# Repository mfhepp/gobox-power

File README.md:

**Note:** This is work-in-progress. I will remove this message when the materials are ready for use.

# DC-DC Boost Converter with Input and Output Filter for QRP Transceivers
This project contains the necessary files and assembly instructions for a small PCB that includes a
a) DC-DC boost converter with effective input and output filters and a
b) battery voltage indicator circuit.

The board was designed for the [Mountain Topper SOTA GoBox](https://github.com/mfhepp/gobox) project, but can be used for any other similar project.

The boost converter is carefully designed to minimize RF emissions and noise on the output and output so that it does not impact the reception of weak radio signals in amateur radio transceivers. 

## Use with 4 NimH Cells ##
In the current form, the circuit will generate 6, 9 or 12 V from a 4 - 6 V input source, like four AA-sized NiMH batteries. This will give roughly 1 , 2.5 and 5 W output power with a Mountain Topper transceiver.

## Use with 2S Lipo Batteries ##
By modifying R4 and R5 one can also produce other voltages. The design can also be used with two LiPo cells, but then a simple SPST switch should be used for SW1 so that it optionally connects R5 parallel to R2. R4 can be omitted in this case, and only 9 or 12 V will be selectable.

You will also have to replace the Zener diode D3 to a type with Zener voltage of ca. 6.2 V so that the low battery warning will use the proper voltages for LiPos (see below).

## Input Current ##
The input current must not exceed 1.4 A, and the input voltage must be lower or equal to the lowest output voltage.

The input current is roughly the output current times the ratio of output voltage to input voltage plus the losses as the inverse of the efficiency (80 - 90%).

`input_current = output_current * output_voltage / (input_voltage * 0.85)`

**You also have to make sure that the battery used can handle the peak input current!!!** Check the datasheet of the battery before usage.

Design decisions will also be included in the final version.

## Low Battery Warning ##
The circuit includes a low battery warning component, but it is up to the user to actually turn of the circuit. As the battery voltages decreases, the red LED ("LOW1") wil start to light, and the green LED ("PWR1") will dim and eventually go out completely.

The exact voltage is determined by the Zener diode D3. For NiMH batteries with four cells, use a 3.9V type. For 2S LiPo packs, a 6.2V Zener diode might be a good choice.

**Warning 1:** You should turn off the device as soon as the green LED goes out completely, and switch back to the lower output voltages (6 or 9V) as soon as the red LED starts lighting. Otherwise, you will likely harm your battery, and because of the increasing input current needed to maintain the fixed output voltage, the circuit may overheat.

**Warning 2:** The battery voltage indicator does only consider the total series voltage of all battery cells. If there is an imbalance due to one or more cells being aged or damaged, the low battery warning will come too late. Thus, use the circuit only with factory-assembled multi-cell packs.

## Overview 
tbd

## Circuit Description 
tbd

## Ripple and Noice ##

Below, please find measurements of the remaining ripple and noise. The output voltage shows practically no ripple (less than 12mV Peak-to-Peak), the input voltage very little (ca. 66 mV Peak-to-Peak).

The parameters of the measurement were as follows:<br />
Input voltage: 9V from a 9V block battery.<br />
Load: 100 R resistor<br />
Output voltage: 11.9V<br />
Output current: 119 mA <br />

Measurements taken with a DMM and a Rigol Oscilloskope with a 1.10 probe.

**Input Voltage Ripple and Noise:** <br />

**Output Voltage Ripple and Noise:** <br />

## Part List
An Excel file that can be uploaded to Mouser's BOM tool is included in the repository at

https://github.com/mfhepp/gobox-power/raw/master/hardware/go-box-power.xlsx

## Assembly
**Note:** This is a densely packed PCB design using SMD components in size 0603, and for minimizing EMI, the pads do not have thermal relief, i.e. are directly connected to the copper of the ground signal and other signals. This makes soldering a bit challenging, and reworking even more so. In other words, this should not be your first exercise in SMD soldering....

The components are placed with minimal distances, so when hand-soldering, you need to think carefull about the ordering of components. Some pads will become hard to reach for hand-soldering once the adjacent component will have been added.

Because of the lack of thermal relief and the pads, you need to use a higher soldering temperature (I found 400 °C to work well), but this in turn means you have to work swiftly. I recommend a flat 1.2mm tip and a round 0.4 mm tip for the work. Preheating the PCB might be a good idea. You also need the finest rosin-core solder you can get hold of.

## Sources
The files in the repository contain 
* Gerber and drill files for producing your own PCBs, and
* a KiCad project with the schematics, PCB, and parts and footprints libraries.

KiCad is a great and free electronics design package. For more information, see [http://kicad.org/](http://kicad.org/).

## Acknowledgments
tbd

## Disclaimer 
THE SOFTWARE AND DESIGN ARE PROVIDED "AS IS", WITHOUT WARRANTY OF ANY KIND, EXPRESS OR IMPLIED, INCLUDING BUT NOT LIMITED TO THE WARRANTIES OF MERCHANTABILITY, FITNESS FOR A PARTICULAR PURPOSE AND NONINFRINGEMENT. IN NO EVENT SHALL THE AUTHORS OR COPYRIGHT HOLDERS BE LIABLE FOR ANY CLAIM, DAMAGES OR OTHER LIABILITY, WHETHER IN AN ACTION OF CONTRACT, TORT OR OTHERWISE, ARISING FROM, OUT OF OR IN CONNECTION WITH THE SOFTWARE OR DESIGN OR THE USE OR OTHER DEALINGS IN THE SOFTWARE OR DESIGN.

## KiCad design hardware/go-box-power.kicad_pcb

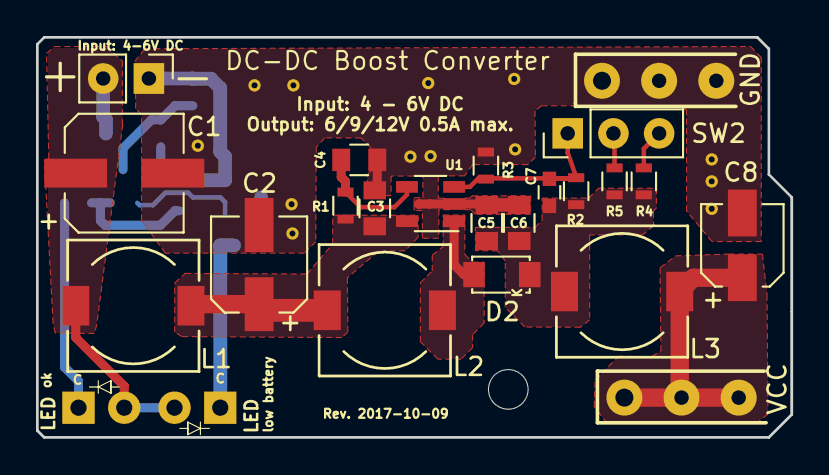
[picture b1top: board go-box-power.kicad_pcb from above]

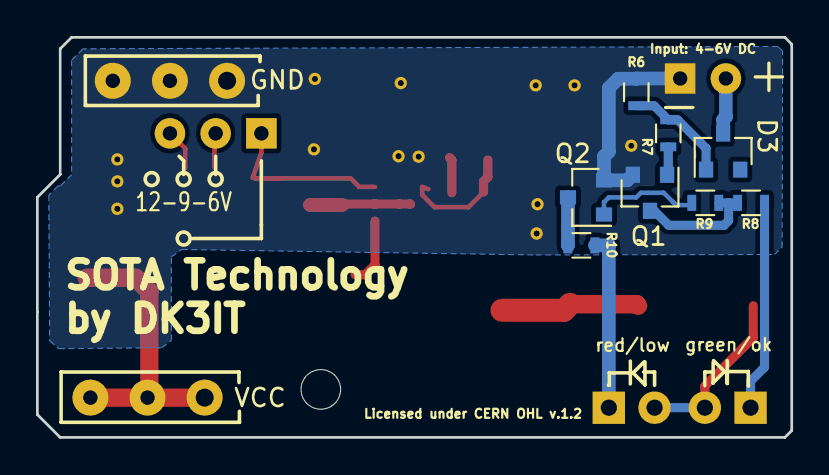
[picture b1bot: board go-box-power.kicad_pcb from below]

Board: 2 copper layers, 41.9 x 22.2 mm, 38 parts (8 on the bottom side), 17 nets.

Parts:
BT1: 4.8V 4-cell NiMH Battery; not_on_board
C1: 33u/16V low ESR; CP_Elec_6.3x5.3
C2: 47u/16V; CP_Elec_5x5.8
C3, C4, C5, C6: 10u/25V; C_0805
C7: 15p; C_0603
C8: 10u/25V; CP_Elec_4x5.8
CHARGE1: 2.5MM; not_on_board
D1: 1N5822; not_on_board
D2: SS14L; D_SubSMA
D3: BZX84-3.9V; SOT-23
EXT_BATTERY1: 2.1MM; not_on_board
F1: Polyfuse 1.85/3A; not_on_board
J1: DC_JACK; Generic_2-Pin_Connector_0.8mm
J2: RIG_VCC; SolderWirePad_3x_0-8mmDrill
J3: RIG_GND; SolderWirePad_3x_0-8mmDrill
L1, L2, L3: 4.7u/2A; Choke_SMD_7.3x7.3_H4.5
LOW1: red; LED_D3.0mm-external
PWR1: green; LED_D3.0mm-external
Q1, Q2: BC847; SOT-23
R1: 100k; R_0603
R2: 430k; R_0603
R3: 51k; R_0603
R4: 360k; R_0603
R5: 1.2M; R_0603
R6: 1k; R_0603
R7: 10k; R_0603
R8, R10: 220; R_0603
R9: 47k; R_0603
SW1: ON; not_on_board
SW2: PWR_LEVEL; SW2-3pins
U1: SC4503; TSOT-23-5

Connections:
BATT_GND: C1.2, C2.2, C3.2, C4.2, C5.2, C6.2, C8.2, J1.1, J3.1, Q1.2, Q2.2, R3.2, R6.1, U1.2
BATT_VCC: C1.1, D3.3, J1.2, L1.1, LOW1.2, PWR1.2
unnamed: C2.1, C3.1, L1.2, L2.1, R1.1, U1.5
unnamed: C4.1, R1.2, U1.4
unnamed: C5.1, C6.1, C7.1, D2.1, L3.1, R2.1, R4.1, R5.1
unnamed: C7.2, R2.2, R3.1, SW2.1, U1.3
unnamed: D2.2, L2.2, U1.1
unnamed: D3.1, R6.2, R7.2
unnamed: LOW1.1, R10.2
unnamed: PWR1.1, R8.2
unnamed: Q1.1, R7.1
unnamed: Q1.3, R8.1, R9.2
unnamed: Q2.1, R9.1
unnamed: Q2.3, R10.1
unnamed: R4.2, SW2.3
unnamed: R5.2, SW2.2
RIG_VCC: C8.1, J2.1, L3.2

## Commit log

2017-11-14 initial version
2017-11-14 added README.md
2017-11-14 minor
2017-11-27 fixed C7 footprint; README.md, measurements
2017-11-28 added part list to README.md
2021-11-10 Update README.md
    https://forum.kicad.info/t/warning-avoid-all-links-to-kicad-pcb-org-use-kicad-org/31521

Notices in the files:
hardware/go-box-power.kicad_pcb:
Licensed under CERN OHL v.1.2
